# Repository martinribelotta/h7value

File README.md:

# STM32H7 value line small board

Simple board for stm32h750 value line device in LQFP100 package.

> Require KiCAD 5.0 or higer

#### Design rules:

- Track/Clearance width: 8mils/8mils
- Drill dia: 0.3048 mm
- Via dia: 0.4064 mm

#### Board contents:

- STM32H750VBT6: 1MBy RAM, 128KBy Flash at 400MHz CPU
- External flash in QSPI1 interface with execute in place (4, 8 or 16MBytes)
- USB HS and FS
- Ethernet PHY in RMII interface (optional)
- MicroSD card in 1bit interface
- 8MHz main crystal
- 32.768KHz RTC crystal
- SWD connector
- Reset button
- User button connected to PA13-WakeUP
- User led connected to PA8
- BOOT dip switch
- 800mA 3.3v regulator
- Others GPIO connected to 100mils-space pin header

#### Dimensions:

#### Schematics:

#### BOM and Gerbers

- [ ] BOM: TODO
- [ ] Gerber: TODO

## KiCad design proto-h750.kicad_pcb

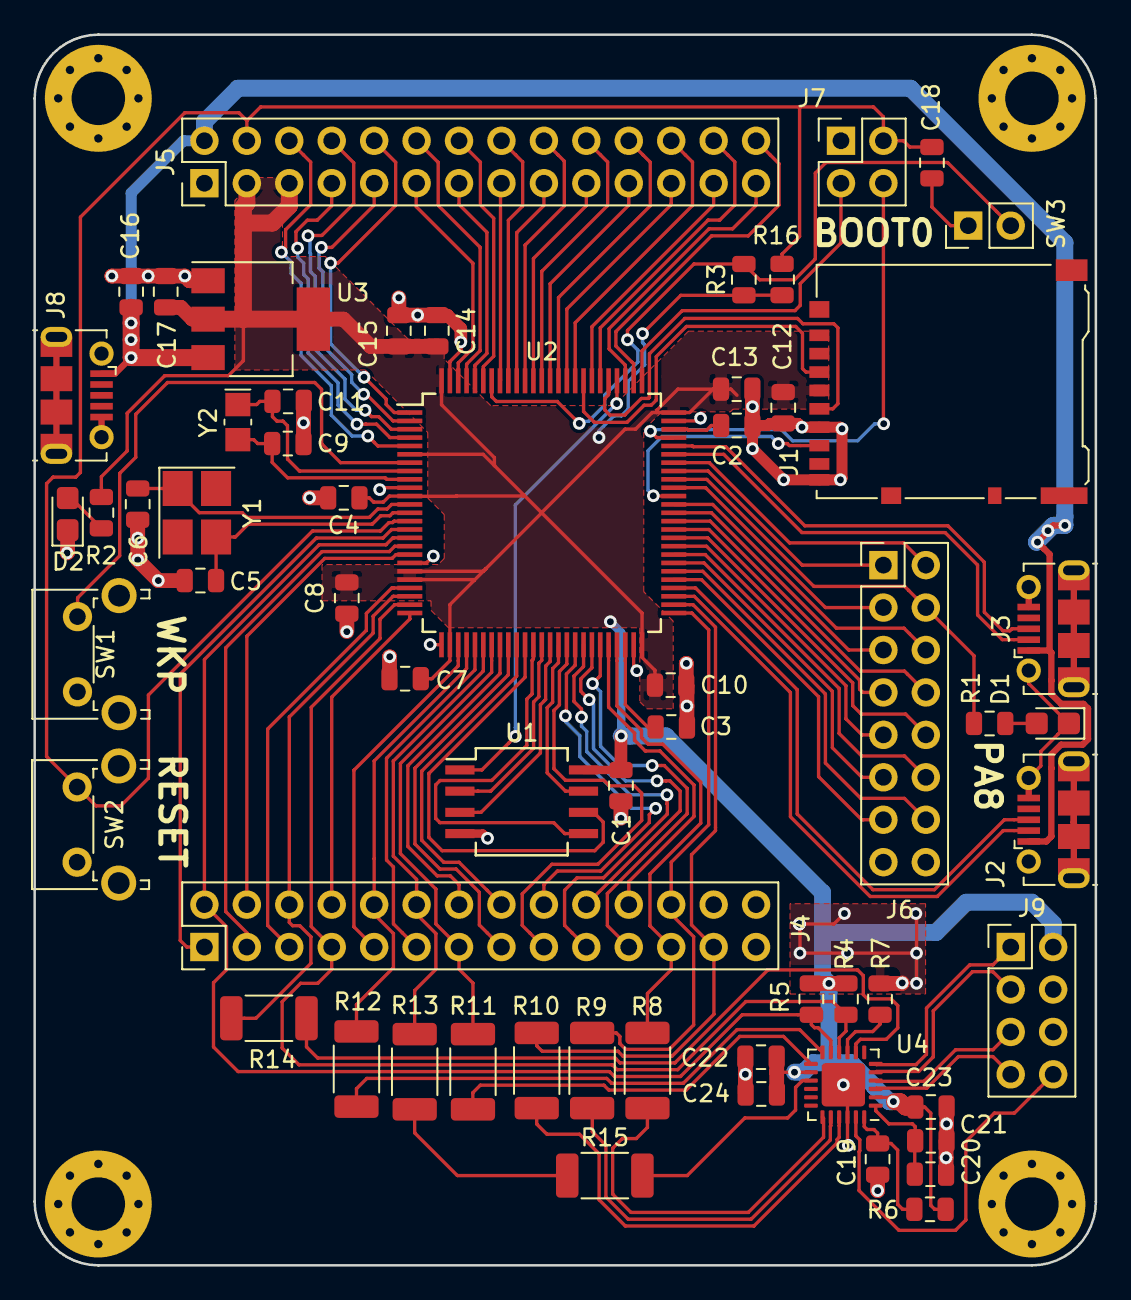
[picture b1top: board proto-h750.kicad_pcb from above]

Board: 2 copper layers, 63.5 x 73.7 mm, 64 parts (0 on the bottom side), 107 nets.

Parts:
C1, C2, C3, C4, C7, C8, C10, C12, C13, C14, C18, C19, C22, C23: 100n; C_0805_2012Metric
C5, C6, C9, C11: 18p; C_0805_2012Metric
C15, C21, C24: 4.7u; C_0805_2012Metric
C16, C17: 10u; C_0805_2012Metric
C20: 2.2u; C_0805_2012Metric
D1, D2: RED; LED_0805_2012Metric_Castellated
H1, H2, H3, H4: MountingHole_Pad; MountingHole_3.2mm_M3_Pad_Via
J1: Micro_SD_Card; microSD_HC_Hirose_DM3AT-SF-PEJM5
J2, J3, J8: USB_B_Micro; USB_Micro-B_Molex-105017-0001
J4, J5: Conn_02x14_Odd_Even; PinHeader_2x14_P2.54mm_Vertical
J6: Conn_02x08_Odd_Even; PinHeader_2x08_P2.54mm_Vertical
J7: Conn_02x02_Odd_Even; PinHeader_2x02_P2.54mm_Vertical
J9: Conn_02x04_Odd_Even; PinHeader_2x04_P2.54mm_Vertical
R1, R2: 220R; R_0805_2012Metric
R3, R4, R5, R6, R16: 10K; R_0805_2012Metric
R7: 6.49K 1%; R_0805_2012Metric
R8, R9, R10, R11, R12, R13, R14, R15: 0R; R_2010_5025Metric
SW1, SW2: SW_Push; SW_Tactile_SPST_Angled_PTS645Vx31-2LFS
SW3: SW_DIP_x01; PinHeader_1x02_P2.54mm_Vertical
U1: S25FL132K0XMFI010; SO-8_5.3x6.2mm_P1.27mm
U2: STM32H750VBT6; LQFP-100_14x14mm_P0.5mm
U3: AP1117-33; SOT-223-3_TabPin2
U4: KSZ8081RNA; QFN-24-1EP_4x4mm_P0.5mm_EP2.6x2.6mm
Y1: 16MHz; Crystal_SMD_3225-4Pin_3.2x2.5mm_HandSoldering
Y2: 32.768KHz; Crystal_SMD_MicroCrystal_CC8V-T1A-2Pin_2.0x1.2mm_HandSolder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

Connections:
+5V: C16.2, J2.1, J3.1, J5.2, J8.1, U3.3
/BOOT: R3.2, SW3.2, U2.94
/ENET_CLK: R14.1, U4.8
/ENET_CRSDV: R15.2, U4.15
/ENET_MDC: J4.2, R5.2, U2.16, U4.11
/ENET_MDIO: J4.7, R4.2, U2.24, U4.10
/ENET_RXD0: R11.1, U4.13
/ENET_RXD1: R12.1, U4.12
/ENET_TXD0: R9.1, U4.20
/ENET_TXD1: R10.1, U4.21
/ENET_TXEN: R8.1, U4.19
/ETH_LED: J9.8, U4.23
/ETH_RX+: J9.5, U4.4
/ETH_RX-: J9.7, U4.3
/ETH_TX+: J9.1, U4.6
/ETH_TX-: J9.3, U4.5
/IO0: U1.5, U2.37
/IO1: U1.2, U2.38
/IO2: U1.3, U2.39
/IO3: U1.7, U2.40
/PA0: J4.5, U2.22
/PA1: J4.6, R14.2, U2.23
/PA3: J4.8, U2.25
/PA4: J4.9, U2.28
/PA5: J4.10, R12.2, U2.29
/PA6: J4.11, U2.30
/PA7: J4.12, R13.2, U2.31
/PA8: J6.4, R1.2, U2.67
/PA9: J6.1, U2.68
/PA10: J6.2, U2.69
/PA15: J5.28, U2.77
/PB0: J4.15, U2.34
/PB1: J4.16, U2.35
/PB3: J5.19, U2.89
/PB4: J5.18, U2.90
/PB5: J5.17, U2.91
/PB6: J5.16, U2.92
/PB7: J5.15, U2.93
/PB8: J5.14, U2.95
/PB9: J5.13, U2.96
/PB10: J4.22, U2.46
/PB11: J4.23, R8.2, U2.47
/PB12: J4.24, R9.2, U2.51
/PB13: J4.25, R10.2, U2.52
/PC0: J4.1, U2.15
/PC2: J4.3, U2.17
/PC3: J4.4, U2.18
/PC4: J4.13, R11.2, U2.32
/PC5: J4.14, U2.33
/PC6: J6.5, U2.63
/PC7: J6.6, U2.64
/PC9: J6.3, U2.66
/PC10: J5.27, U2.78
/PC13: SW1.2, U2.7
/PD0: J5.26, U2.81
/PD1: J5.25, U2.82
/PD3: J5.24, U2.84
/PD4: J5.23, U2.85
/PD5: J5.22, U2.86
/PD6: J5.21, U2.87
/PD7: J5.20, U2.88
/PD8: J6.13, U2.55
/PD9: J6.14, U2.56
/PD10: J6.11, U2.57
/PD11: J6.12, U2.58
/PD12: J6.9, U2.59
/PD13: J6.10, U2.60
/PD14: J6.7, U2.61
/PD15: J6.8, U2.62
/PE0: J5.12, U2.97
/PE1: J5.11, U2.98
/PE2: J5.10, U2.1
/PE3: J5.9, U2.2
/PE4: J5.8, U2.3
/PE5: J5.7, U2.4
/PE6: J5.6, U2.5
/PE11: J4.17, U2.41
/PE12: J4.18, U2.42
/PE13: J4.19, U2.43
/PE14: J4.20, U2.44
/PE15: J4.21, U2.45
/SCLK: U1.6, U2.36
/SD_CK: J1.5, U2.80
/SD_CMD: J1.3, U2.83
/SD_D0: J1.7, U2.65
/SWCLK: J7.3, U2.76
/SWDIO: J7.4, U2.72
/USB0_D+: J2.3, U2.54
/USB0_D-: J2.2, U2.53
/USB1_D+: J3.3, U2.71
/USB1_D-: J3.2, U2.70
/nCS: U1.1, U2.79
/nRESET: C18.1, J5.4, J7.2, R16.2, SW2.2, U2.14
GND: C1.2, C2.2, C3.2, C4.2, C5.1, C6.1, C7.2, C8.2, C9.1, C10.2, C11.1, C12.2, C13.2, C14.1, C15.2, C16.1, C17.2, C18.2, C19.1, C20.1, C21.1, C22.1, C23.1, C24.1, D1.1, D2.1, H1.1, H2.1, H3.1, H4.1, J1.6, J1.9, J2.5, J2.6, J3.5, J3.6, J4.26, J4.27, J4.28, J5.1, J6.15, J6.16, J7.1, J8.5, J8.6, J9.4, J9.6, R7.1, SW1.1, SW2.1, SW3.1, U1.4, U2.10, U2.19, U2.26, U2.49, U2.74, U2.99, U3.1, U4.22, U4.25
unnamed: C2.1, U2.73
unnamed: C3.1, U2.48
unnamed: C5.2, U2.13, Y1.3
unnamed: C6.2, U2.12, Y1.1
unnamed: C9.2, U2.9, Y2.2
unnamed: C11.2, U2.8, Y2.1
unnamed: C19.2, R6.2, U4.24
unnamed: C20.2, C21.2, U4.1
unnamed: D1.2, R1.1
unnamed: D2.2, R2.1
unnamed: R7.2, U4.9
unnamed: R13.1, R15.1
VCC: C1.1, C4.1, C7.1, C8.1, C10.1, C12.1, C13.1, C14.2, C15.1, C17.1, C22.2, C23.2, C24.2, J1.4, J5.3, J5.5, J9.2, R2.2, R3.1, R4.1, R5.1, R6.1, R16.1, U1.8, U2.6, U2.11, U2.20, U2.21, U2.27, U2.50, U2.75, U2.100, U3.2, U4.2, U4.14

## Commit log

2018-11-14 Add eth phy
2018-11-14 Add README, create schematics and put measures in PCB
2018-11-14 Fix image url
2018-11-16 Change dimention annotations
2018-11-18 Prepare to BOM
    - Change BOOT switch by jumper
    - Change 32.768KHz footprint by 2SMD 2.0x1.2mm
    - Change 8MHz 4SMD by same footprint in 16MHz
    - Add Part number field of all schematic items
2018-11-18 Prepare to BOM (2)
    - Change resistor of 22R in ETH PHY by 0R
2018-11-18 Prepare to BOM (3)
    - Add pull-up on reset
    - Generate Gerbers in protel format-name
